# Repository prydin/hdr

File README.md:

# Hardware Defined Radio
This is currently just a testbed for some of my experiments. Not much to see yet...

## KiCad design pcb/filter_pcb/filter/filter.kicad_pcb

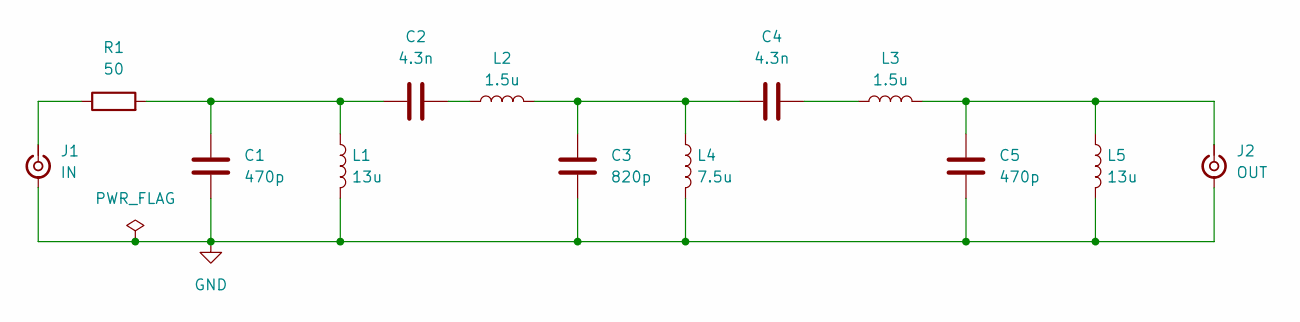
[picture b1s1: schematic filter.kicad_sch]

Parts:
C1, C5: 470p; C_Disc_D3.8mm_W2.6mm_P2.50mm
C2, C4: 4.3n; C_Disc_D3.8mm_W2.6mm_P2.50mm
C3: 820p; C_Disc_D3.8mm_W2.6mm_P2.50mm
J1: IN; SMA_Amphenol_901-144_Vertical
J2: OUT; SMA_Amphenol_901-144_Vertical
L1, L5: 13u; L_Toroid_Vertical_L10.0mm_W5.0mm_P5.08mm
L2, L3: 1.5u; L_Toroid_Vertical_L10.0mm_W5.0mm_P5.08mm
L4: 7.5u; L_Toroid_Vertical_L10.0mm_W5.0mm_P5.08mm
R1: 50; R_Axial_DIN0204_L3.6mm_D1.6mm_P7.62mm_Horizontal

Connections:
GND: C1.2, C3.1, C5.2, J1.2 (Ext), J2.2 (Ext), L1.2, L4.2, L5.2
unnamed: C3.2, C4.1, L2.2, L4.1
unnamed: C1.1, C2.1, L1.1, R1.2
unnamed: C2.2, L2.1
unnamed: C4.2, L3.1
unnamed: J1.1 (In), R1.1
unnamed: C5.1, J2.1 (In), L3.2, L5.1

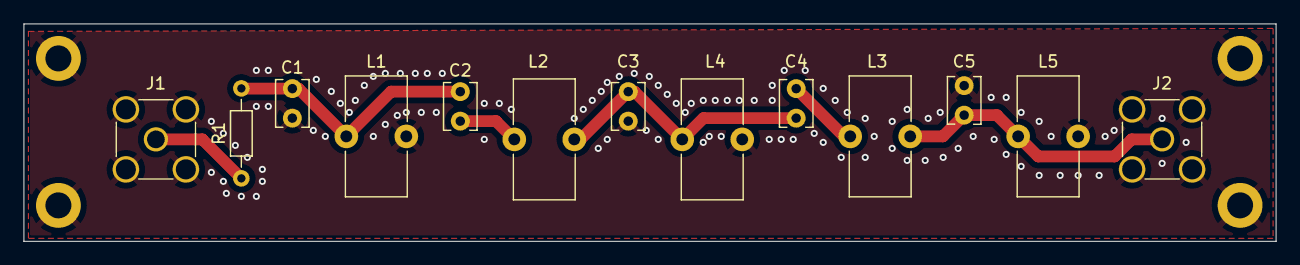
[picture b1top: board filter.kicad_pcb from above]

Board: 2 copper layers, 106.0 x 18.4 mm, 13 parts (0 on the bottom side), 7 nets.

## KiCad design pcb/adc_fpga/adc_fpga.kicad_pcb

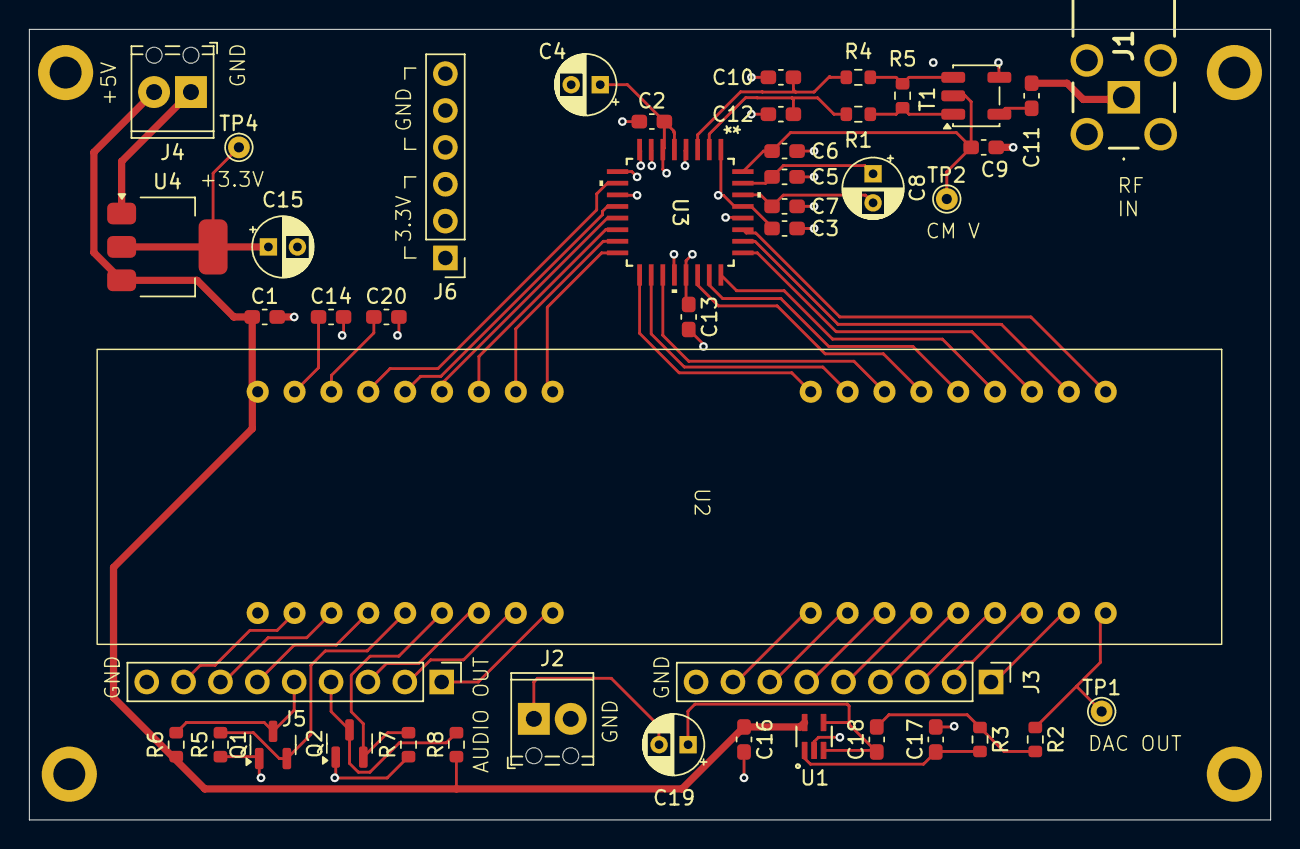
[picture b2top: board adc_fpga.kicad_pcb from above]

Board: 4 copper layers, 85.5 x 54.5 mm, 45 parts (0 on the bottom side), 52 nets.

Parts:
C1, C2, C3, C5, C6, C7, C9, C11, C13, C14, C16, C20: 100n; C_0603_1608Metric_Pad1.08x0.95mm_HandSolder
C4, C8, C15, C19: 10u; CP_Radial_D4.0mm_P2.00mm
C10, C12: 100p; C_0603_1608Metric_Pad1.08x0.95mm_HandSolder
C17: 470p; C_0603_1608Metric_Pad1.08x0.95mm_HandSolder
C18: 1n; C_0603_1608Metric_Pad1.08x0.95mm_HandSolder
J1: RF_IN; RF203NT0050GRP
J2, J4: TerminalBlock_Phoenix_MPT-0,5-2-2.54_1x02_P2.54mm_Horizontal
J3, J5: AUX I/O; PinHeader_1x09_P2.54mm_Vertical
J6: PinHeader_1x06_P2.54mm_Vertical
Q1, Q2: BSS138; SOT-23
R1, R4: 33; R_0603_1608Metric
R2, R5#2, R6, R7, R8: 10k; R_0603_1608Metric
R3: 15k; R_0603_1608Metric
R5: 50; R_0603_1608Metric
T1: Transformer_MiniCircuits_AT224-1A
TP1: DAC OUT; TestPoint_THTPad_D1.5mm_Drill0.7mm
TP2: CM; TestPoint_THTPad_D1.5mm_Drill0.7mm
TP4: +3.3V; TestPoint_THTPad_D1.5mm_Drill0.7mm
U1: MAX4230AXK; SOT65P210X110-5N
U2: CMOD S7
U3: ADC14L020CIVY/NOPB; VBE32A_TEX
U4: TLV76133DCY; SOT-223-3_TabPin2

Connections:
+3.3V: C2.2, C3.2, C4.1, C13.1, C15.1, J6.1, J6.2, J6.3, Q1.1 (G), Q2.1 (G), R5#2.1, R7.1, TP4.1, U3.1 (VREF), U3.5 (VA), U3.6 (VD), U3.21 (VDR), U3.29 (VA), U4.2 (VO)
+5V: C1.1, C16.1, J4.2, R6.1, R8.1, U1.5 (V+), U2.24 (VU), U4.3 (VI)
GND: C1.2, C2.1, C3.1, C4.2, C5.1, C6.1, C7.1, C9.2, C10.1, C12.2, C13.2, C14.2, C15.2, C16.2, C17.2, C20.2, J1.2 (Ext), J2.2, J3.9, J4.1, J5.9, J6.4, J6.5, J6.6, T1.4, U1.2 (V-), U2.25 (GND), U3.4 (AGND), U3.7 (AGND), U3.8 (PD), U3.9 (DGND), U3.11 (DF/DCS), U3.20 (DRGND), U3.28 (AGND), U4.1 (GND)
unnamed: C11.2, T1.6
unnamed: C18.2, R2.2, R3.1
unnamed: C11.1, J1.1 (In)
unnamed: C19.2, J2.1
unnamed: R1.2, R5.1, T1.1
unnamed: R4.2, R5.2, T1.3
unnamed: C17.1, R3.2, U1.1 (+)
unnamed: C18.1, C19.1, U1.3 (-), U1.4
unnamed: J3.7, U2.41 (A2)
unnamed: J3.1, U2.47 (A3)
unnamed: R2.1, TP1.1, U2.48 (A4)
unnamed: J5.2, U2.32 (A32)
unnamed: J5.1, U2.33 (A33)
unnamed: J3.5, U2.43 (B1)
unnamed: J3.6, U2.42 (B2)
unnamed: J3.3, U2.45 (B3)
unnamed: J3.2, U2.46 (B4)
unnamed: J3.4, U2.44 (C1)
unnamed: J3.8, U2.40 (C5)
unnamed: J5.3, U2.31 (J11)
unnamed: J5.6, U2.28 (J15)
unnamed: J5.7, U2.27 (K14)
unnamed: U2.1 (L1), U3.27 (D13(MSB))
unnamed: J5.8, U2.26 (L14)
unnamed: C14.1, U2.23 (L15)
unnamed: U2.5 (M2), U3.23 (D9)
unnamed: U2.3 (M3), U3.25 (D11)
unnamed: U2.2 (M4), U3.26 (D12)
unnamed: C20.1, U2.22 (M14)
unnamed: U2.21 (M15), U3.10 (CLK)
unnamed: U2.9 (N1), U3.17 (D5)
unnamed: U2.4 (N2), U3.24 (D10)
unnamed: U2.7 (N3), U3.19 (D7)
unnamed: U2.18 (N13), U3.14 (D2)
unnamed: U2.20 (N14), U3.12 ((LSB)D0)
unnamed: U2.19 (N15), U3.13 (D1)
unnamed: U2.8 (P1), U3.18 (D6)
unnamed: U2.6 (P3), U3.22 (D8)
unnamed: U2.16 (P14), U3.16 (D4)
unnamed: U2.17 (P15), U3.15 (D3)
unnamed: C12.1, R1.1, U3.2 (VIN+)
unnamed: C10.2, R4.1, U3.3 (VIN-)
unnamed: C6.2, C9.1, T1.2, TP2.1, U3.32 (VRM)
unnamed: C7.2, C8.2, U3.30 (VRN)
unnamed: C5.2, C8.1, U3.31 (VRP)
SCL3.3V: Q1.2 (S), R5#2.2, U2.29 (L13)
SCL5V: J5.5, Q1.3 (D), R6.2
SDA3.3V: Q2.2 (S), R7.2, U2.30 (M13)
SDA5V: J5.4, Q2.3 (D), R8.2

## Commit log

2024-06-10 Moved PCB designs from old project
2024-06-11 Compact design
2024-06-25 LCD kind of working
2024-06-28 Working LCD
2024-06-28 Working fq display code
